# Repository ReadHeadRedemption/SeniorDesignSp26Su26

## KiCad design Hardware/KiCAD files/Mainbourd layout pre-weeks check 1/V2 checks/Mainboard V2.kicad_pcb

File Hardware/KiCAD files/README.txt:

The master schematic is within "Senior design mainboard32826 backup" 

This was the version that everything was verified in as of 4/10/2026

Then for the sake of layout, and neatness broken out into their own project files for each discrete board.
This includes swapping and non-swapping

as of 6/4/2026 

Mainbourd layout pre-weeks check 1 has most up to date version of mainboard PCB this will eventually be made neater again as development continues but this is noted to avoid mistakes for now

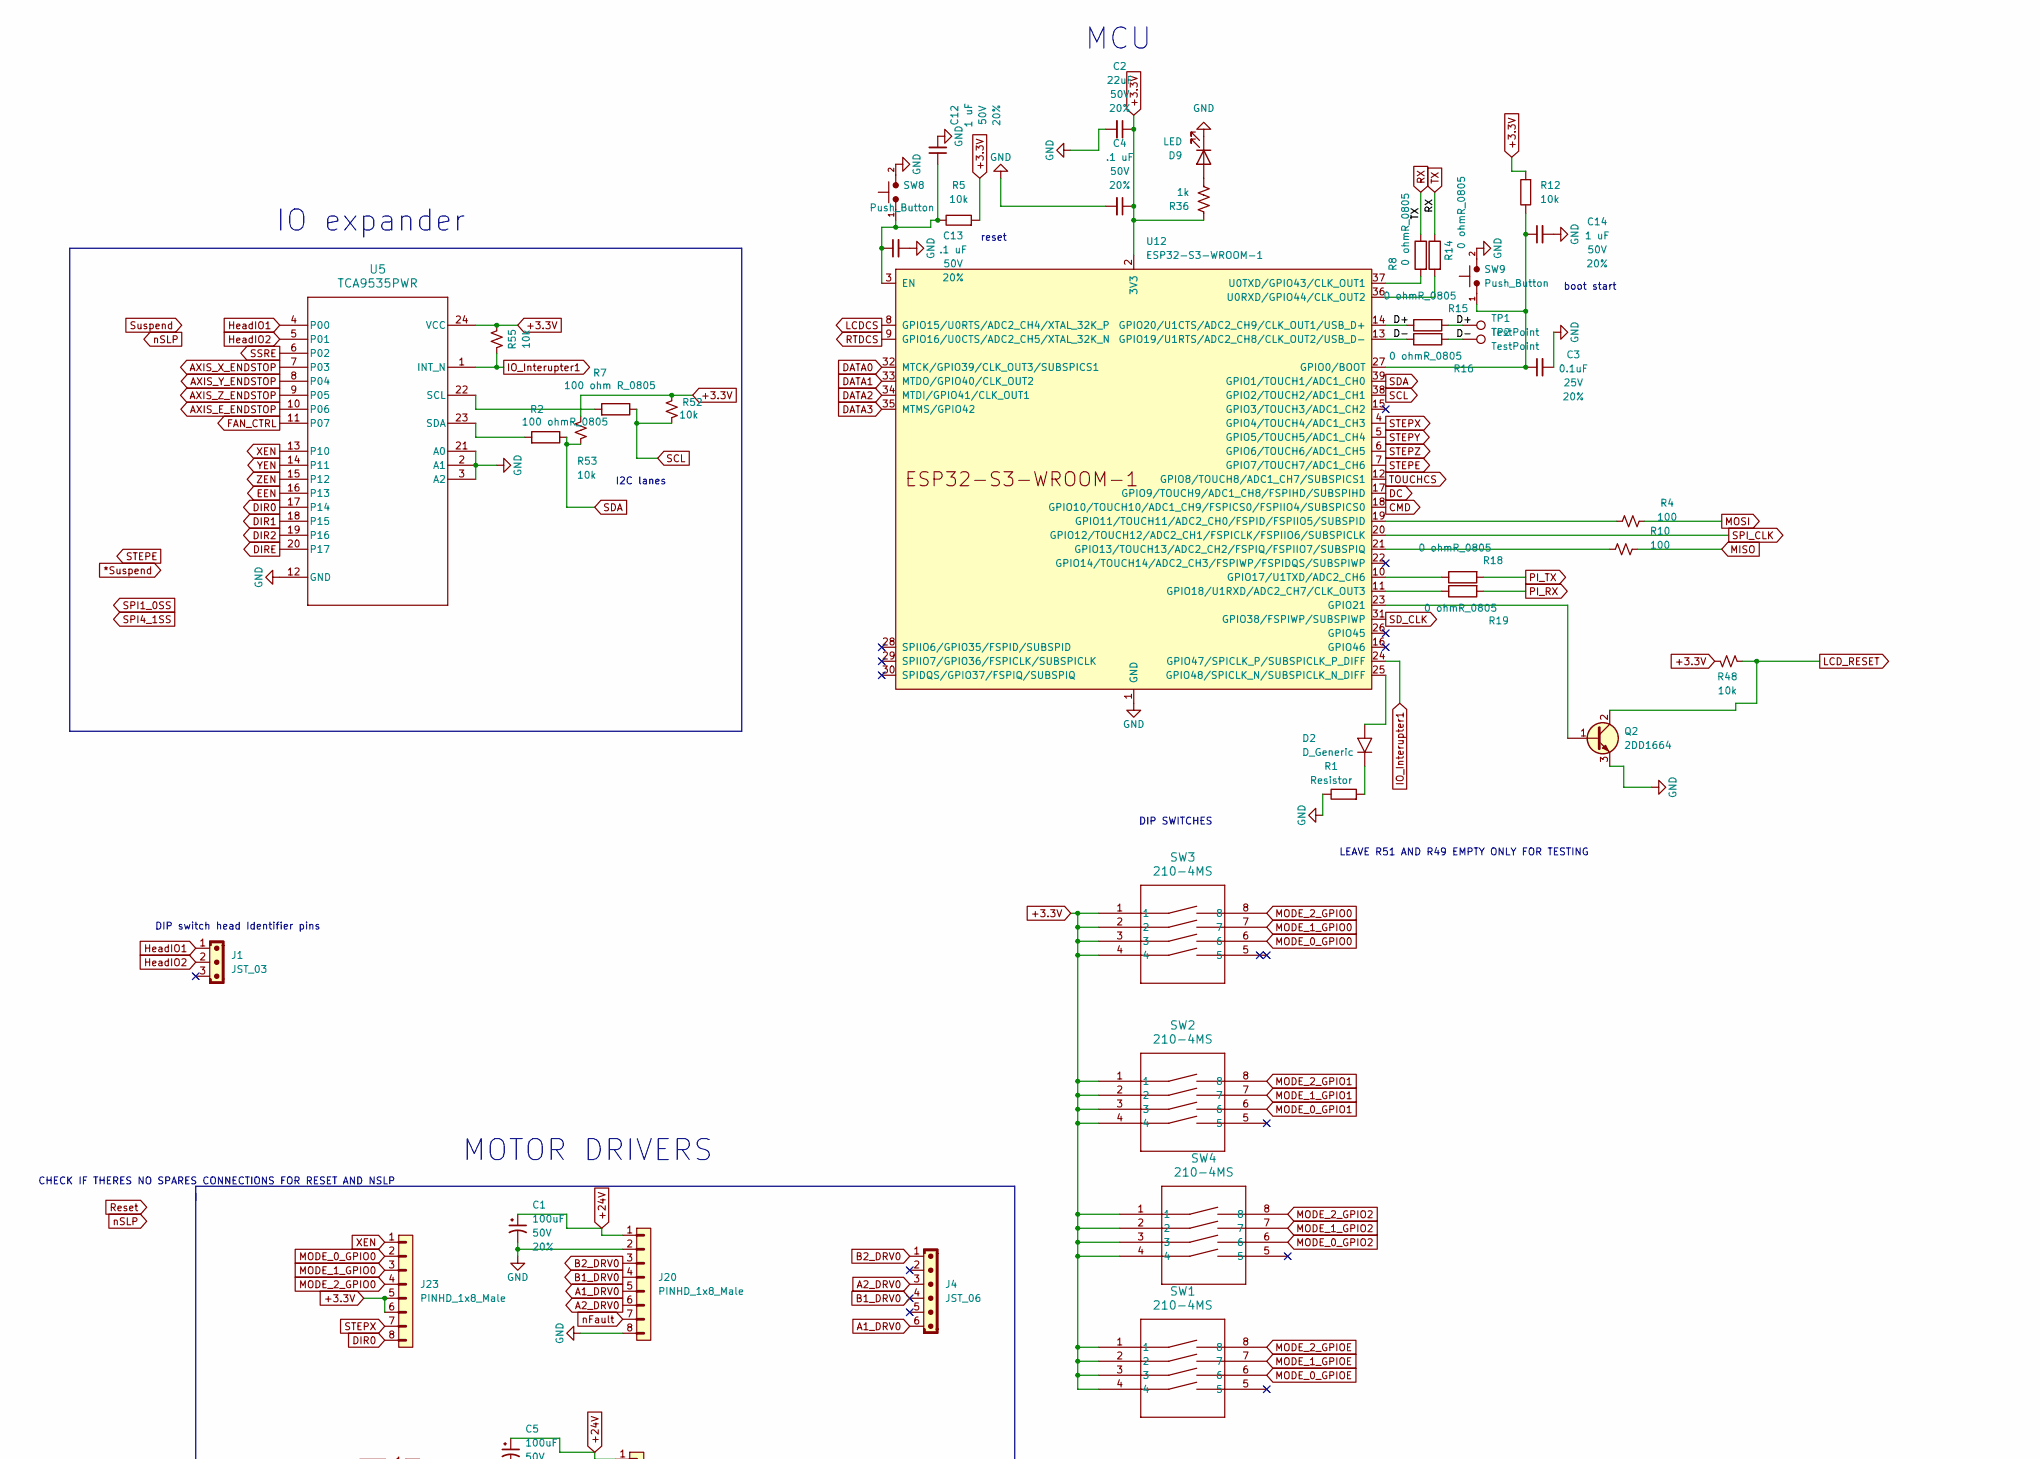
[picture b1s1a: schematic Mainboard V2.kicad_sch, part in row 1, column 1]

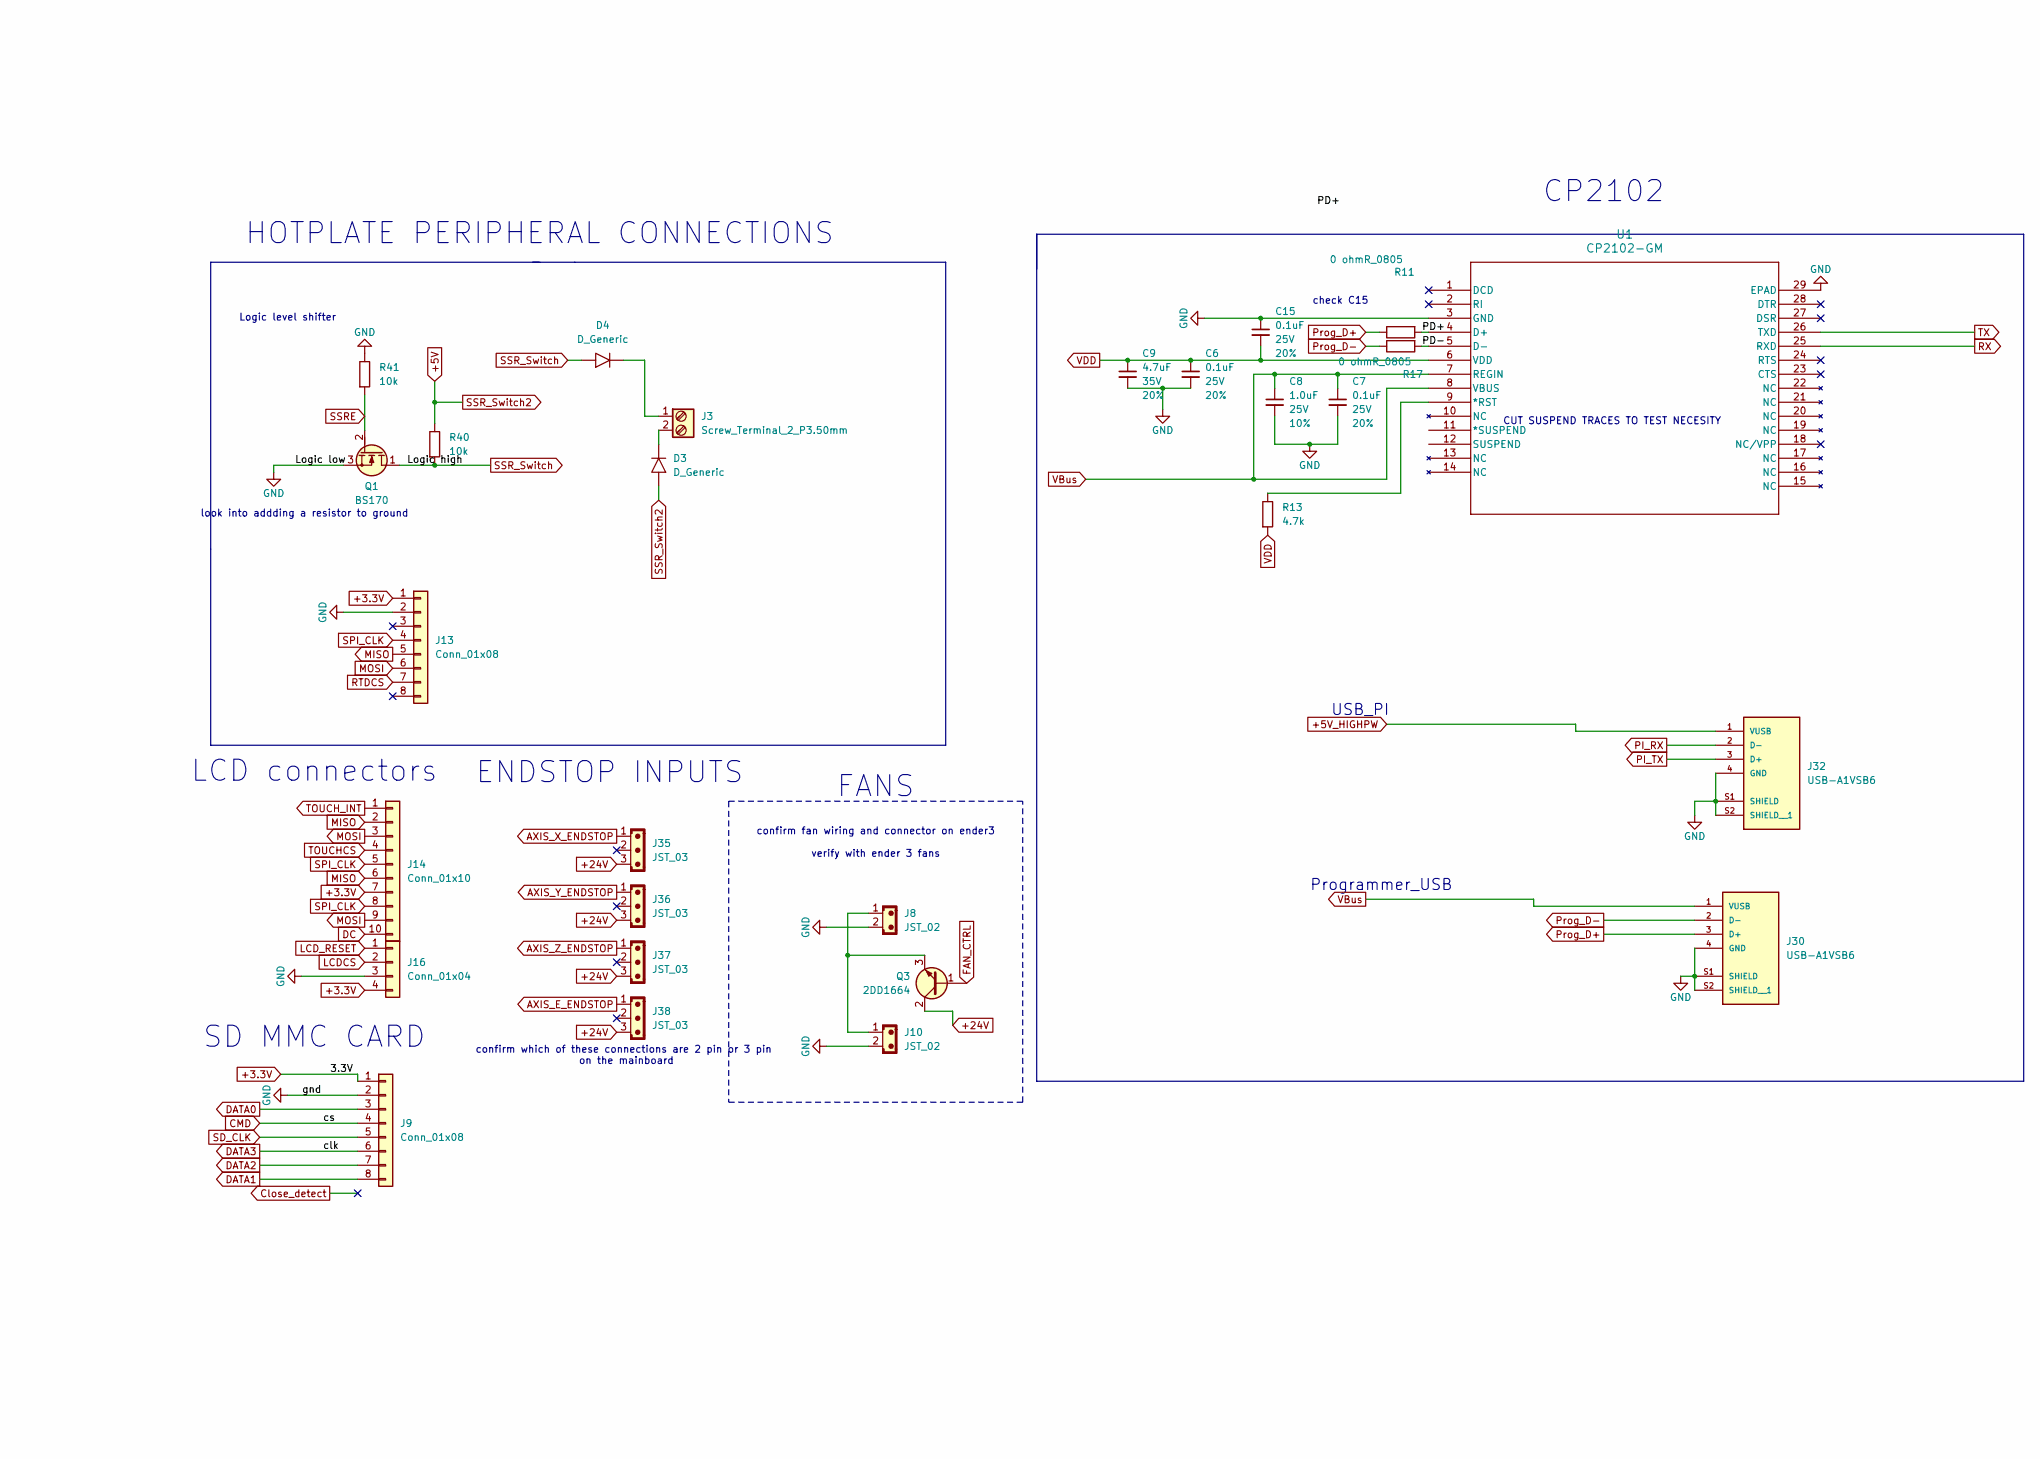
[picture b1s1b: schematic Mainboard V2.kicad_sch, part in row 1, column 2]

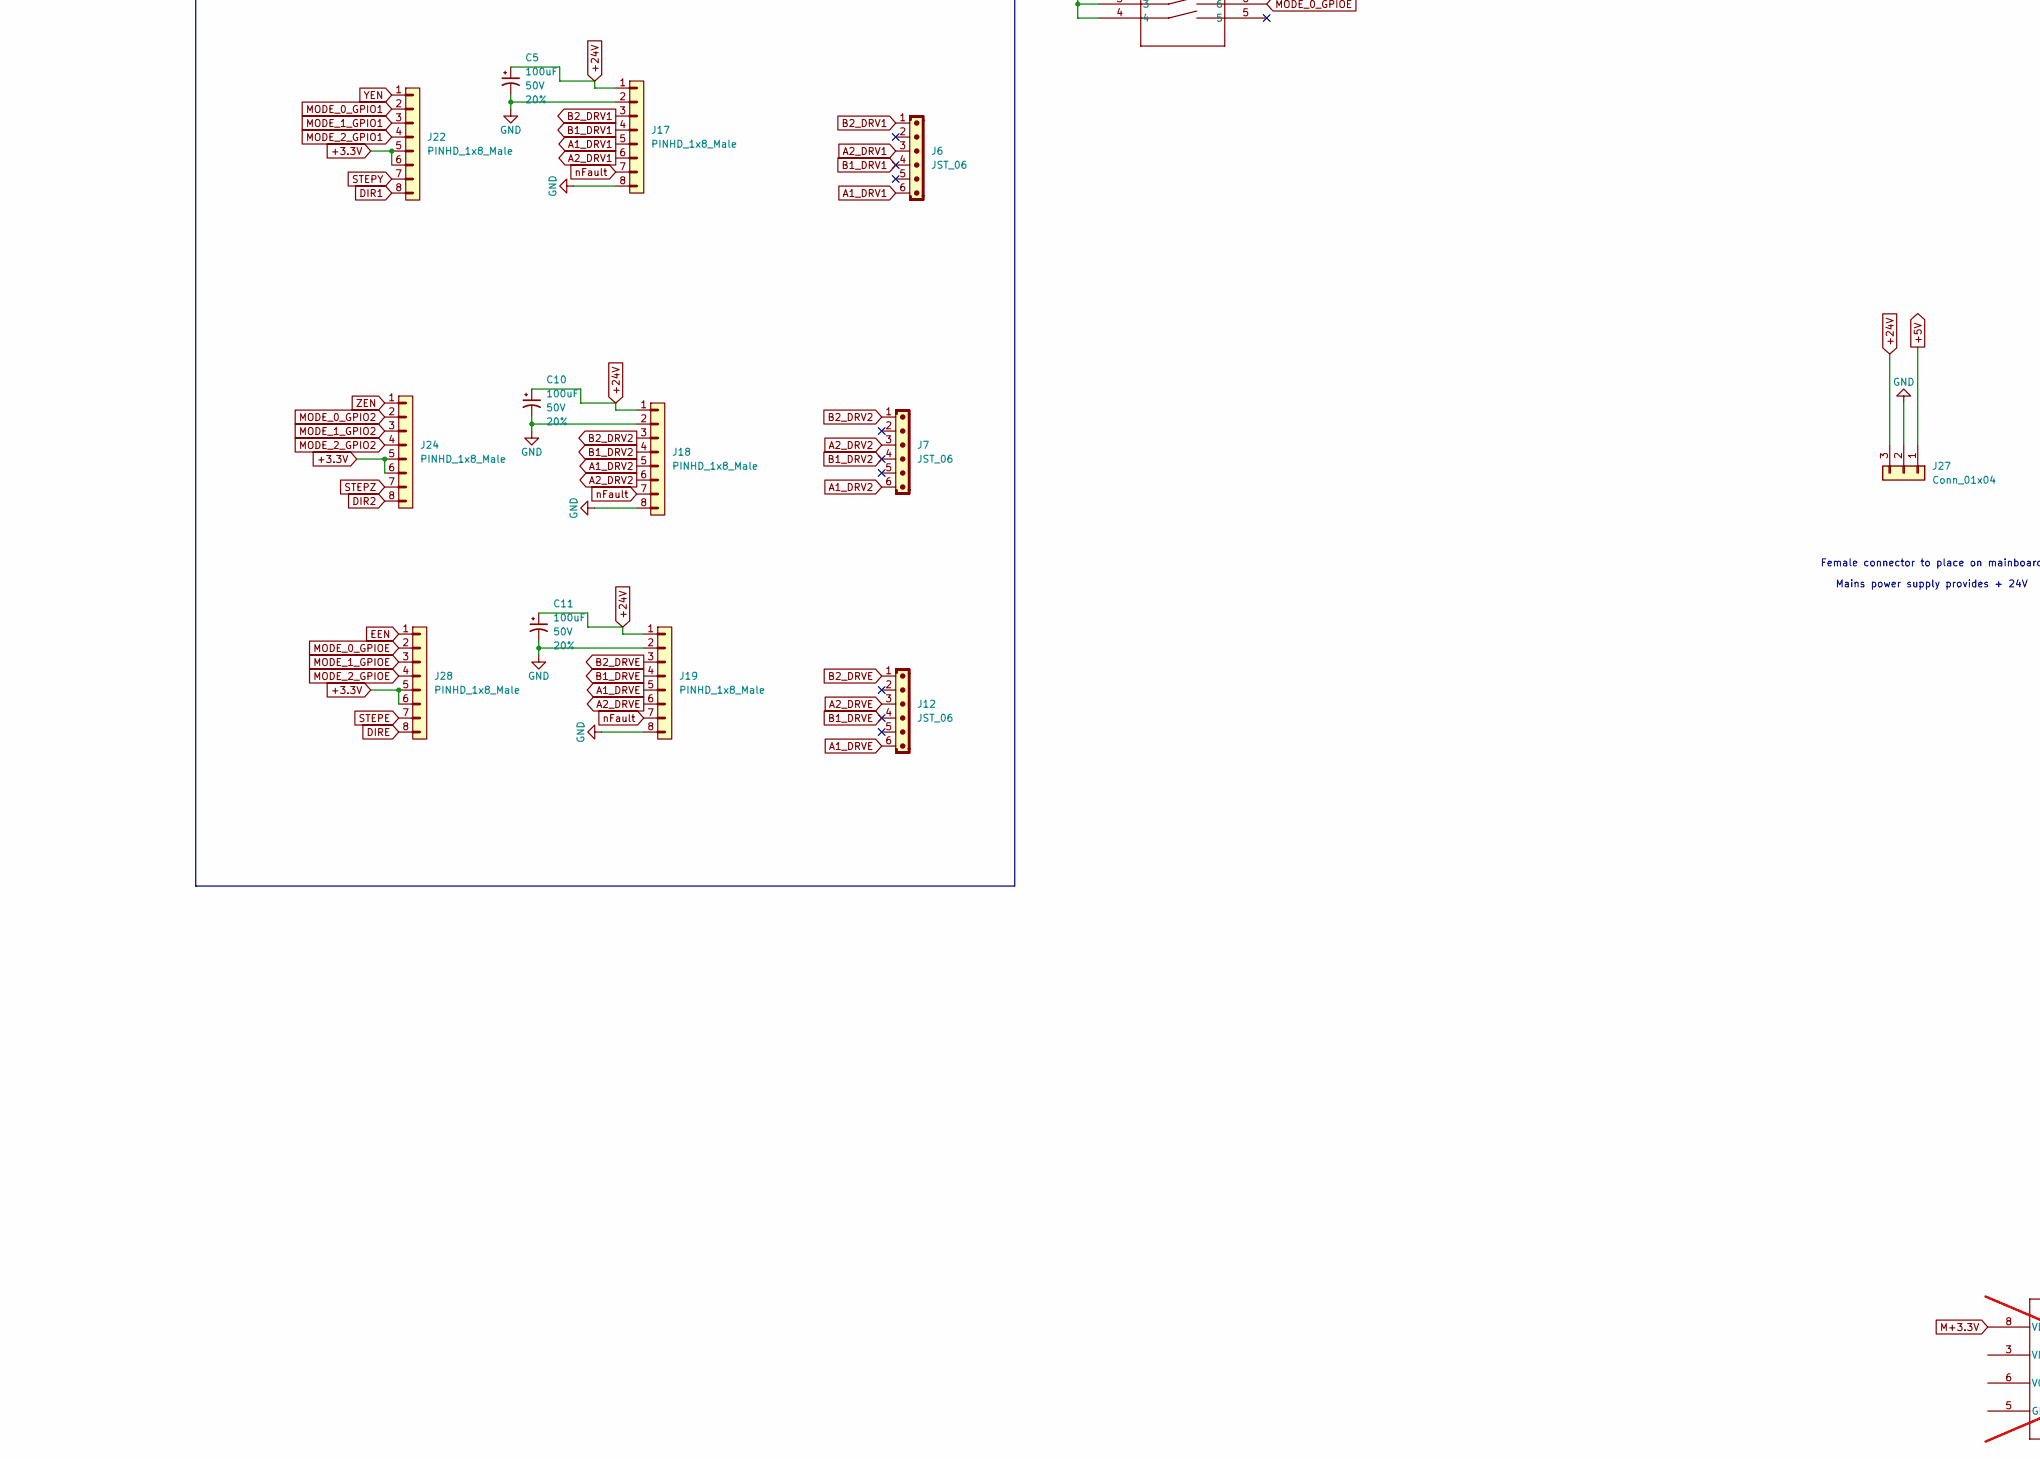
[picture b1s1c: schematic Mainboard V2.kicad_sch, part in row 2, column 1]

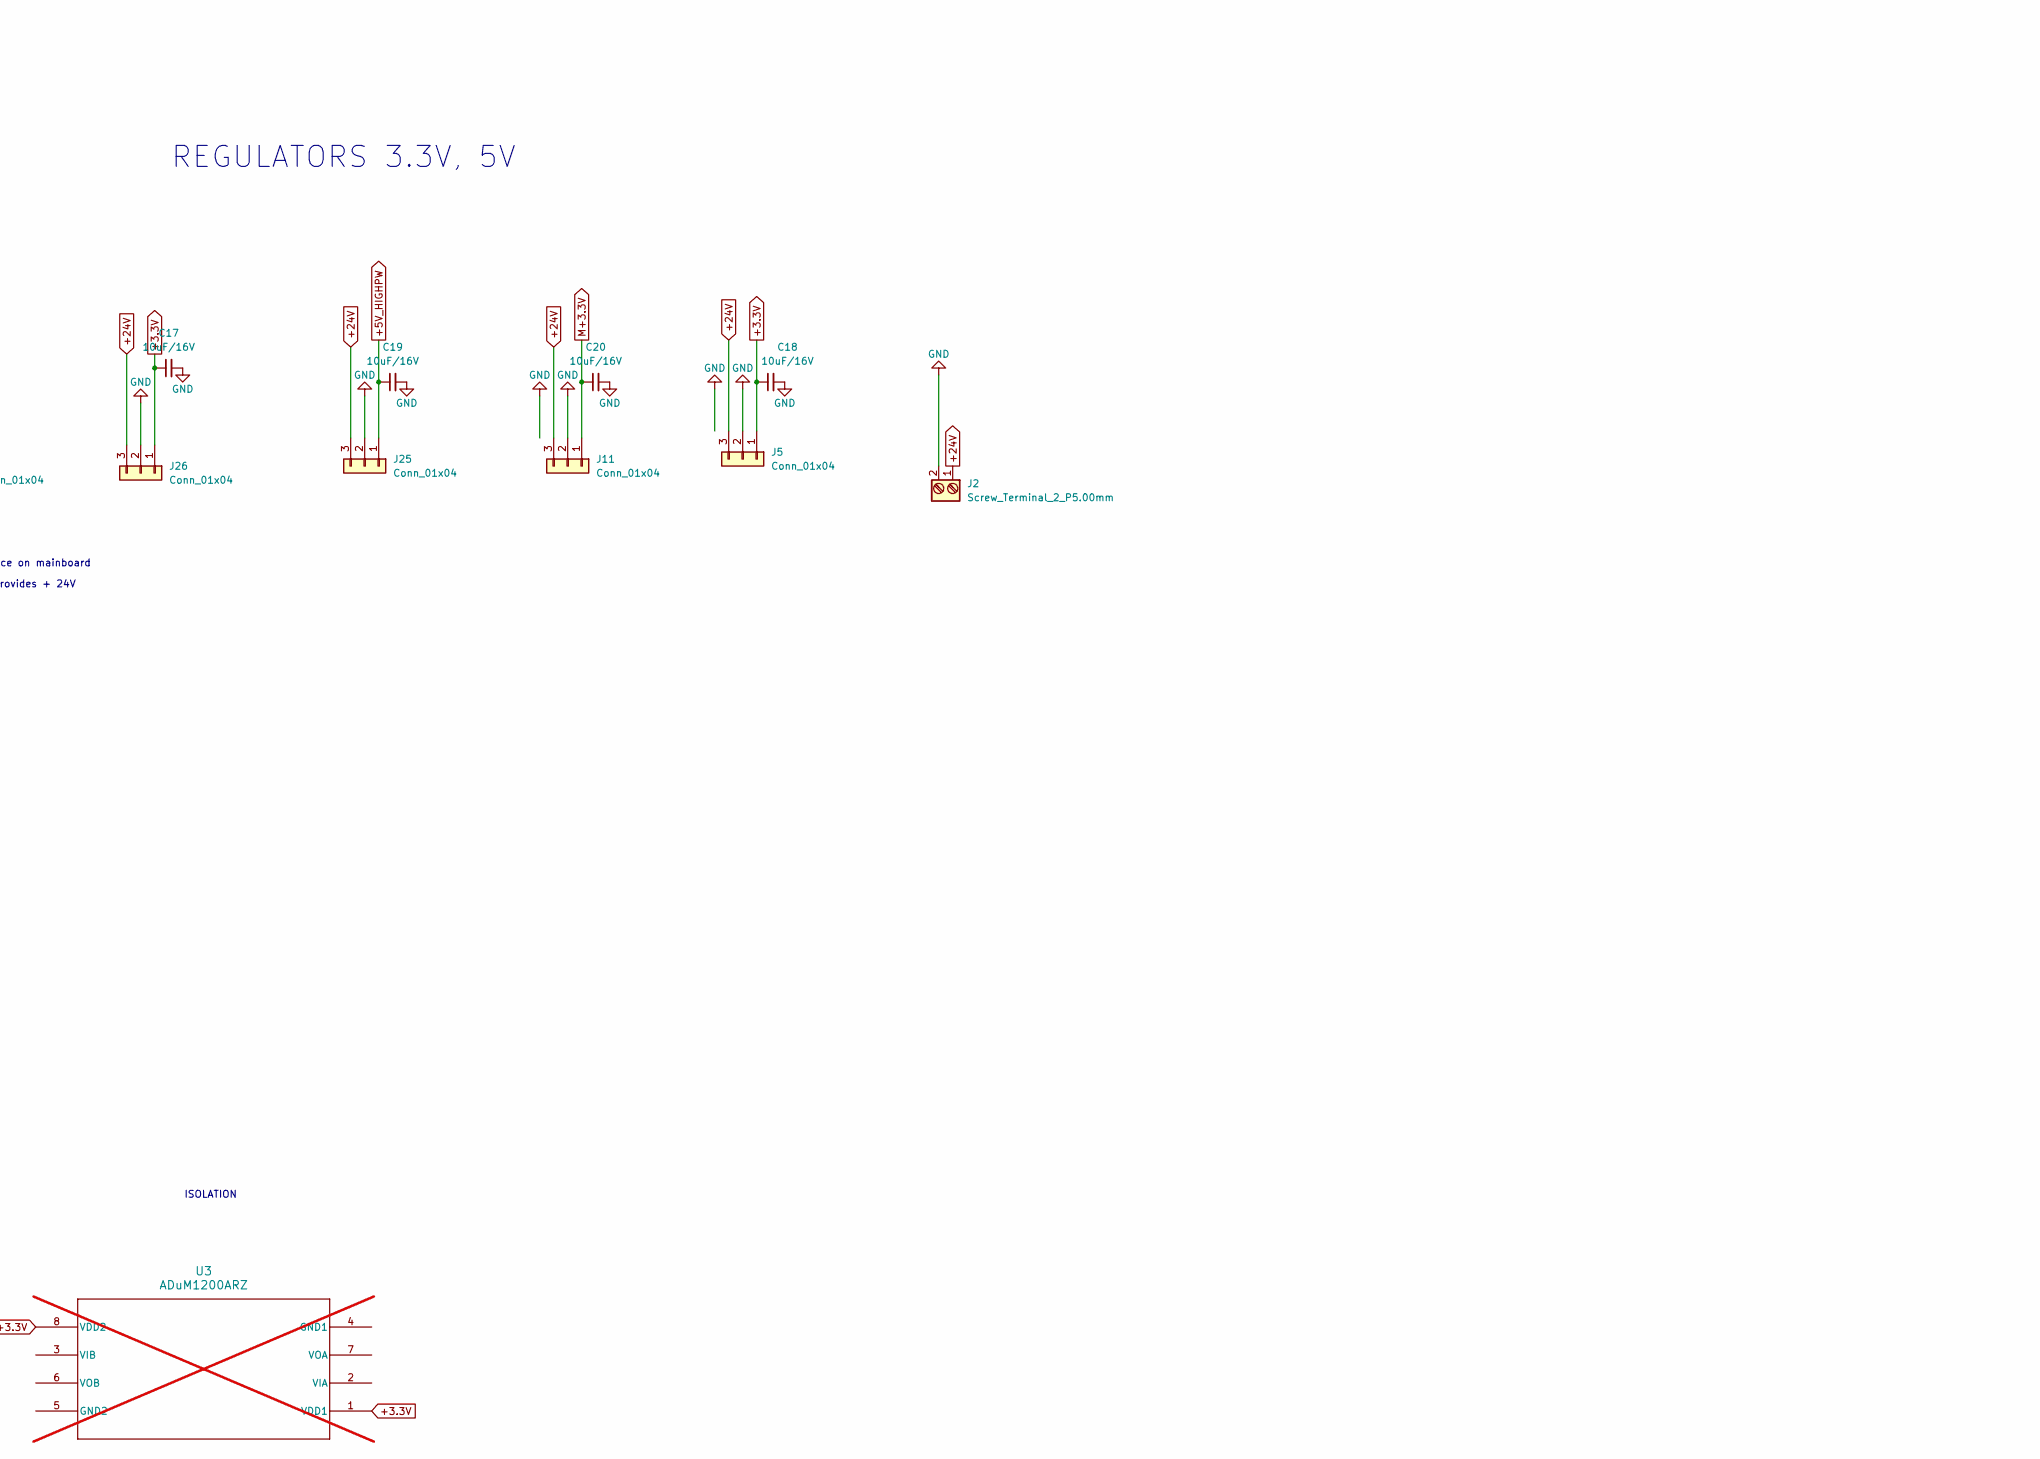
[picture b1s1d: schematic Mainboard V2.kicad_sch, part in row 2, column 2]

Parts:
C1, C5, C10, C11: 100uF; C_Rect_L11.0mm_W3.5mm_P10.00mm_MKT; Voltage 50V; Tolerance 20%
C2: 22uF; C_1210_3225Metric; Voltage 50V; Tolerance 20%
C3, C6, C7, C15: 0.1uF; C_0805_2012Metric; Voltage 25V; Tolerance 20%
C4, C13: .1 uF; C_1210_3225Metric; Voltage 50V; Tolerance 20%
C8: 1.0uF; C_0805_2012Metric; Voltage 25V; Tolerance 10%
C9: 4.7uF; C_0805_2012Metric; Voltage 35V; Tolerance 20%
C12, C14: 1 uF; C_1210_3225Metric; Voltage 50V; Tolerance 20%
C17, C18, C19, C20: 10uF_1210_35V; C_1210_3225Metric; Part Number GMK325BJ106MN-T; JLCPCB ID C172721
D2: D_Generic
D3, D4: D_Generic; D_DO-201AD_P15.24mm_Horizontal
D9: LED; LED_0603_1608Metric
J1, J35, J36, J37, J38: JST_03; JST_EH_B3B-EH-A_1x03_P2.50mm_Vertical
J2: Screw_Terminal_2_P5.00mm; TerminalBlock_Phoenix_PT-1,5-2-5.0-H_1x02_P5.00mm_Horizontal
J3: Screw_Terminal_2_P3.50mm; TerminalBlock_Phoenix_PT-1,5-2-3.5-H_1x02_P3.50mm_Horizontal
J4, J6, J7, J12: JST_06; JST_EH_B6B-EH-A_1x06_P2.50mm_Vertical
J5, J11, J25, J26, J27: Conn_01x04; 1x03_P2.54mm
J8, J10: JST_02; JST_EH_B2B-EH-A_1x02_P2.50mm_Vertical
J9, J13: Conn_01x08; 1x08_P2.54mm
J14: Conn_01x10; 1x10_P2.54mm
J16: Conn_01x04; 1x04_P2.54mm
J17, J18, J19, J20, J22, J23, J24, J28: PINHD_1x8_Male; PinHeader_1x08_P2.54mm_Vertical
J30, J32: USB-A1VSB6; USB_A_Kycon_KUSBX-AS1N-B_Horizontal; PARTREV D
Q1: BS170; TO-92_Inline_Wide_DGS
Q2, Q3: 2DD1664; SOT-89-3
R1: Resistor; R_Axial_DIN0207_L6.3mm_D2.5mm_P10.16mm_Horizontal
R2: 100 ohmR_0805; R_0805_2012Metric
R4, R10: 100; R_0805_2012Metric
R5, R12, R40, R41: 10k; R_Axial_DIN0207_L6.3mm_D2.5mm_P10.16mm_Horizontal
R7: 100 ohm R_0805; R_0805_2012Metric
R8, R11, R14, R15, R16, R17, R18, R19: 0 ohmR_0805; R_0805_2012Metric
R13: 4.7k; R_Axial_DIN0207_L6.3mm_D2.5mm_P10.16mm_Horizontal
R36: 1k; R_1206_3216Metric_Pad1.30x1.75mm_HandSolder
R48: 10k; R_0603_1608Metric
R52, R53: 10k; LED_0805_2012Metric
R55: 10k; R_0805_2012Metric
SW1, SW2, SW3, SW4: 210-4MS; DIP8_210-4_CTS
SW8, SW9: Push_Button; SW_PUSH_6mm
TP1, TP2: TestPoint; TestPoint_Loop_D2.54mm_Drill1.5mm_Beaded
U1: CP2102-GM; QFN28_5X5_SIL
U3: ADuM1200ARZ; R_8_ADI; not fitted
U5: TCA9535PWR; PW0024A_N
U12: ESP32-S3-WROOM-1

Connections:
+3.3V: C2.1, C4.1, C17.1, C18.1, J5.1, J9.1, J13.1, J14.7, J16.4, J22.5, J22.6, J23.5, J23.6, J24.5, J24.6, J26.1, J28.5, J28.6, R5.1, R12.1, R36.1, R48.1, R52.2, R53.2, R55.1, SW1.1, SW1.2, SW1.3, SW1.4, SW2.1, SW2.2, SW2.3, SW2.4, SW3.1, SW3.2, SW3.3, SW3.4, SW4.1, SW4.2, SW4.3, SW4.4, U3.1 (VDD1), U5.24 (VCC), U12.2 (3V3)
+5V: D3.2 (A), J27.1, R40.2
+5V_HIGHPW: C19.1, J25.1, J32.1 (VUSB)
+24V: C1.1, C5.1, C10.1, C11.1, J2.1, J5.3, J11.3, J17.1, J18.1, J19.1, J20.1, J25.3, J26.3, J27.3, J35.3, J36.3, J37.3, J38.3, Q3.2 (C)
/D+: R15.1, R15.2, TP1.1 (1_1), U12.14 (GPIO20/U1CTS/ADC2_CH9/CLK_OUT1/USB_D+)
/D-: R16.1, R16.2, TP2.1 (1_1), U12.13 (GPIO19/U1RTS/ADC2_CH8/CLK_OUT2/USB_D-)
/PD+: R11.1, U1.4 (D+)
/PD-: R17.1, U1.5 (D-)
A1_DRV0: J4.6, J20.5
A1_DRV1: J6.6, J17.5
A1_DRV2: J7.6, J18.5
A1_DRVE: J12.6, J19.5
A2_DRV0: J4.3, J20.6
A2_DRV1: J6.3, J17.6
A2_DRV2: J7.3, J18.6
A2_DRVE: J12.3, J19.6
AXIS_E_ENDSTOP: J38.1, U5.10 (P06)
AXIS_X_ENDSTOP: J35.1, U5.7 (P03)
AXIS_Y_ENDSTOP: J36.1, U5.8 (P04)
AXIS_Z_ENDSTOP: J37.1, U5.9 (P05)
B1_DRV0: J4.4, J20.4
B1_DRV1: J6.4, J17.4
B1_DRV2: J7.4, J18.4
B1_DRVE: J12.4, J19.4
B2_DRV0: J4.1, J20.3
B2_DRV1: J6.1, J17.3
B2_DRV2: J7.1, J18.3
B2_DRVE: J12.1, J19.3
CMD: J9.4, U12.18 (GPIO10/TOUCH10/ADC1_CH9/FSPICS0/FSPIIO4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)
DATA0: J9.3, U12.32 (MTCK/GPIO39/CLK_OUT3/SUBSPICS1)
DATA1: J9.8, U12.33 (MTDO/GPIO40/CLK_OUT2)
DATA2: J9.7, U12.34 (MTDI/GPIO41/CLK_OUT1)
DATA3: J9.6, U12.35 (MTMS/GPIO42)
DC: J14.10, U12.17 (GPIO9/TOUCH9/ADC1_CH8/FSPIHD/SUBSPIHD)
DIR0: J23.8, U5.17 (P14)
DIR1: J22.8, U5.18 (P15)
DIR2: J24.8, U5.19 (P16)
DIRE: J28.8, U5.20 (P17)
EEN: J28.1, U5.16 (P13)
FAN_CTRL: Q3.1 (B), U5.11 (P07)
GND: C1.2, C2.2, C3.2, C4.2, C5.2, C6.2, C7.2, C8.2, C9.2, C10.2, C11.2, C12.2, C13.2, C14.2, C15.1, C17.2, C18.2, C19.2, C20.2, D9.1 (K), J2.2, J5.2, J8.2, J9.2, J10.2, J11.2, J13.2, J16.3, J17.2, J17.8, J18.2, J18.8, J19.2, J19.8, J20.2, J20.8, J25.2, J26.2, J27.2, J30.4 (GND), J30.S1 (SHIELD), J30.S2 (SHIELD__1), J32.4 (GND), J32.S1 (SHIELD), J32.S2 (SHIELD__1), Q1.3 (S), Q2.3 (E), R1.2, R41.2, SW8.2, SW9.2, U1.3 (GND), U1.29 (EPAD), U5.2 (A1), U5.3 (A2), U5.12 (GND), U5.21 (A0), U12.1 (GND), U12.40 (GND), U12.41 (GND); also elsewhere on the board
HeadIO1: J1.1, U5.4 (P00)
HeadIO2: J1.2, U5.5 (P01)
IO_Interupter1: R55.2, U5.1 (INT_N), U12.24 (GPIO47/SPICLK_P/SUBSPICLK_P_DIFF)
LCDCS: J16.2, U12.8 (GPIO15/U0RTS/ADC2_CH4/XTAL_32K_P)
LCD_RESET: J16.1, Q2.2 (C), R48.2
M+3.3V: C20.1, J11.1, U3.8 (VDD2)
MISO: J13.5, J14.2, J14.6, R10.2
MODE_0_GPIO0: J23.2, SW3.6
MODE_0_GPIO1: J22.2, SW2.6
MODE_0_GPIO2: J24.2, SW4.6
MODE_0_GPIOE: J28.2, SW1.6
MODE_1_GPIO0: J23.3, SW3.7
MODE_1_GPIO1: J22.3, SW2.7
MODE_1_GPIO2: J24.3, SW4.7
MODE_1_GPIOE: J28.3, SW1.7
MODE_2_GPIO0: J23.4, SW3.8
MODE_2_GPIO1: J22.4, SW2.8
MODE_2_GPIO2: J24.4, SW4.8
MODE_2_GPIOE: J28.4, SW1.8
MOSI: J13.6, J14.3, J14.9, R4.2
unnamed: D2.2 (A), U12.25 (GPIO48/SPICLK_N/SUBSPICLK_N_DIFF)
unnamed: D2.1 (K), R1.1
unnamed: D3.1 (K), J3.2
unnamed: D4.1 (K), J3.1
unnamed: D9.2 (A), R36.2
unnamed: Q2.1 (B), U12.23 (GPIO21)
unnamed: J8.1, J10.1, Q3.3 (E)
unnamed: R13.2, U1.9 (*RST)
unnamed: R7.1, U5.22 (SCL)
unnamed: R2.1, U5.23 (SDA)
unnamed 71: C12.1, C13.1, R5.2, SW8.1, U12.3 (EN); also elsewhere on the board
unnamed: C3.1, C14.1, R12.2, SW9.1, U12.27 (GPIO0/BOOT)
unnamed: R4.1, U12.19 (GPIO11/TOUCH11/ADC2_CH0/FSPID/FSPIIO5/S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)
unnamed: R10.1, U12.21 (GPIO13/TOUCH13/ADC2_CH2/FSPIQ/FSPIIO7/S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)
unnamed: R18.2, U12.10 (GPIO17/U1TXD/ADC2_CH6)
unnamed: R19.2, U12.11 (GPIO18/U1RXD/ADC2_CH7/CLK_OUT3)
unnamed: R14.1, U12.36 (U0RXD/GPIO44/CLK_OUT2)
unnamed: R8.1, U12.37 (U0TXD/GPIO43/CLK_OUT1)
PI_RX: J32.2 (D-), R19.1
PI_TX: J32.3 (D+), R18.1
Prog_D+: J30.3 (D+), R11.2
Prog_D-: J30.2 (D-), R17.2
RTDCS: J13.7, U12.9 (GPIO16/U0CTS/ADC2_CH5/XTAL_32K_N)
RX: R8.2, R14.2, U1.25 (RXD), U1.26 (TXD)
SCL: R7.2, R52.1, U12.38 (GPIO2/TOUCH2/ADC1_CH1)
SDA: R2.2, R53.1, U12.39 (GPIO1/TOUCH1/ADC1_CH0)
SD_CLK: J9.5, U12.31 (GPIO38/FSPIWP/SUBSPIWP)
SPI_CLK: J13.4, J14.5, J14.8, U12.20 (GPIO12/TOUCH12/ADC2_CH1/FSPICLK/FSPIIO6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)
SSRE: Q1.2 (G), R41.1, U5.6 (P02)
SSR_Switch: D4.2 (A), Q1.1 (D), R40.1
STEPE: J28.7, U12.7 (GPIO7/TOUCH7/ADC1_CH6)
STEPX: J23.7, U12.4 (GPIO4/TOUCH4/ADC1_CH3)
STEPY: J22.7, U12.5 (GPIO5/TOUCH5/ADC1_CH4)
STEPZ: J24.7, U12.6 (GPIO6/TOUCH6/ADC1_CH5)
TOUCHCS: J14.4, U12.12 (GPIO8/TOUCH8/ADC1_CH7/SUBSPICS1)
TOUCH_INT: J14.1
VBus: C7.1, C8.1, J30.1 (VUSB), U1.7 (REGIN), U1.8 (VBUS)
VDD: C6.1, C9.1, C15.2, R13.1, U1.6 (VDD)
XEN: J23.1, U5.13 (P10)
YEN: J22.1, U5.14 (P11)
ZEN: J24.1, U5.15 (P12)
nFault: J17.7, J18.7, J19.7, J20.7

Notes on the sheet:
ISOLATION
HOTPLATE PERIPHERAL CONNECTIONS
CHECK IF THERES NO SPARES CONNECTIONS FOR RESET AND NSLP
boot start
I2C lanes
USB_PI
Mains power supply provides + 24V
Female connector to place on mainboard
confirm which of these connections are 2 pin or 3 pin on the mainboard
ENDSTOP INPUTS
IO expander
look into addding a resistor to ground
DIP SWITCHES
LCD connectors
LEAVE R51 AND R49 EMPTY ONLY FOR TESTING
CP2102
CUT SUSPEND TRACES TO TEST NECESITY
check C15
SD MMC CARD
FANS
DIP switch head Identifier pins
MCU
REGULATORS 3.3V, 5V
reset
Logic level shifter
MOTOR DRIVERS
confirm fan wiring and connector on ender3 verify with ender 3 fans
Programmer_USB

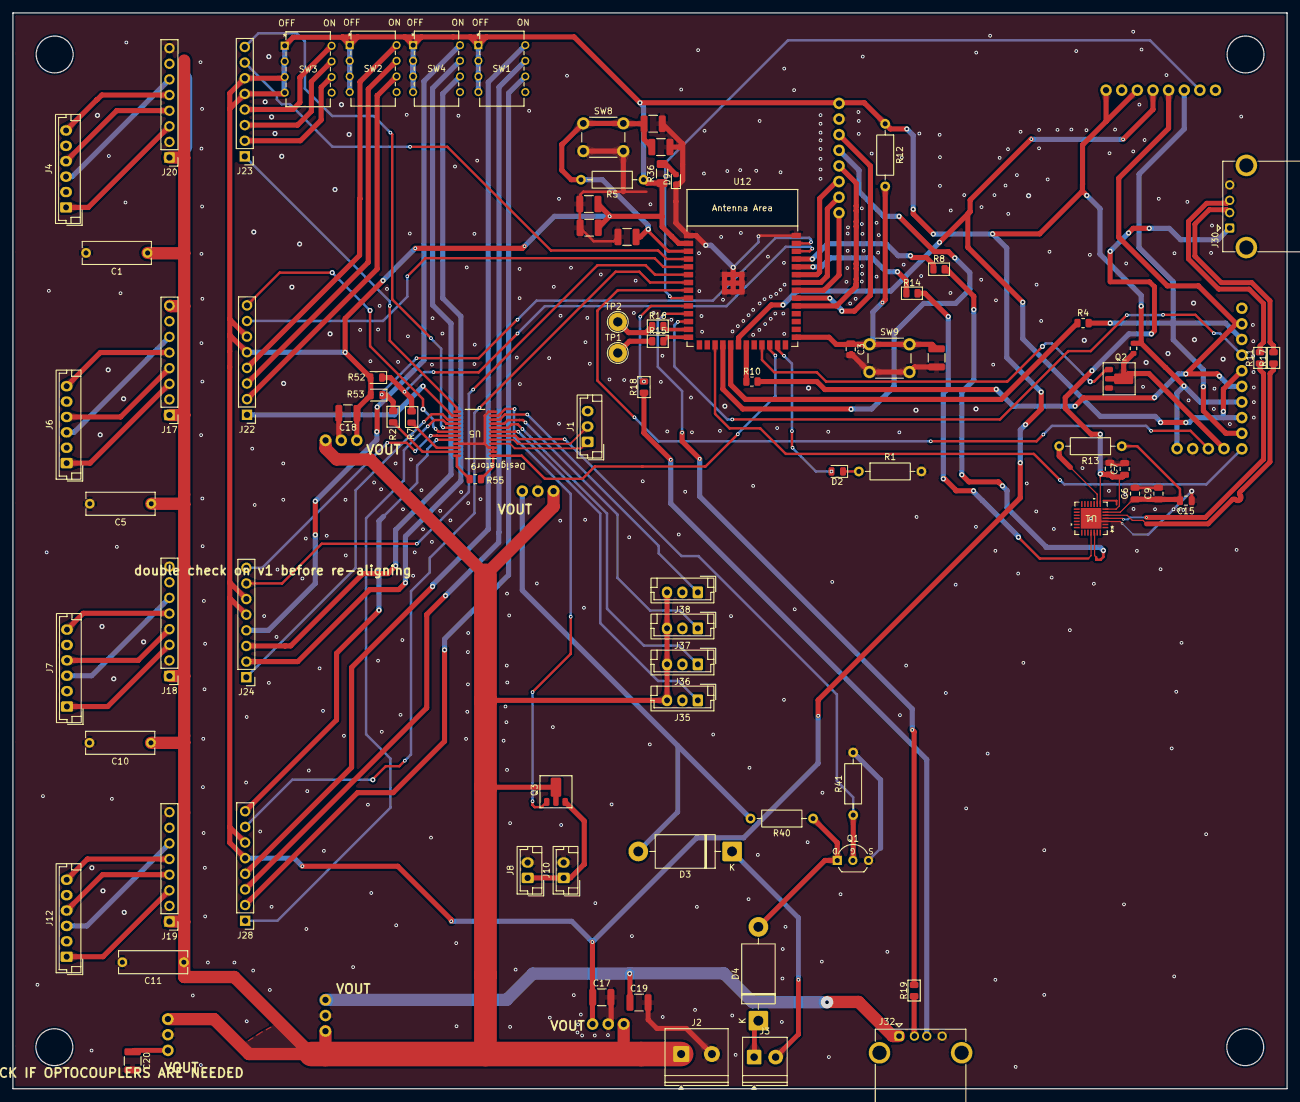
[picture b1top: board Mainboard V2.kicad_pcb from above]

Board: 2 copper layers, 207.0 x 174.8 mm, 93 parts (0 on the bottom side), 102 nets.

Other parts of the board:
C4#2: 10uF; C_1210_3225Metric

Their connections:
GND: C4#2.2; also elsewhere on the board
unnamed 71: C4#2.1; also elsewhere on the board

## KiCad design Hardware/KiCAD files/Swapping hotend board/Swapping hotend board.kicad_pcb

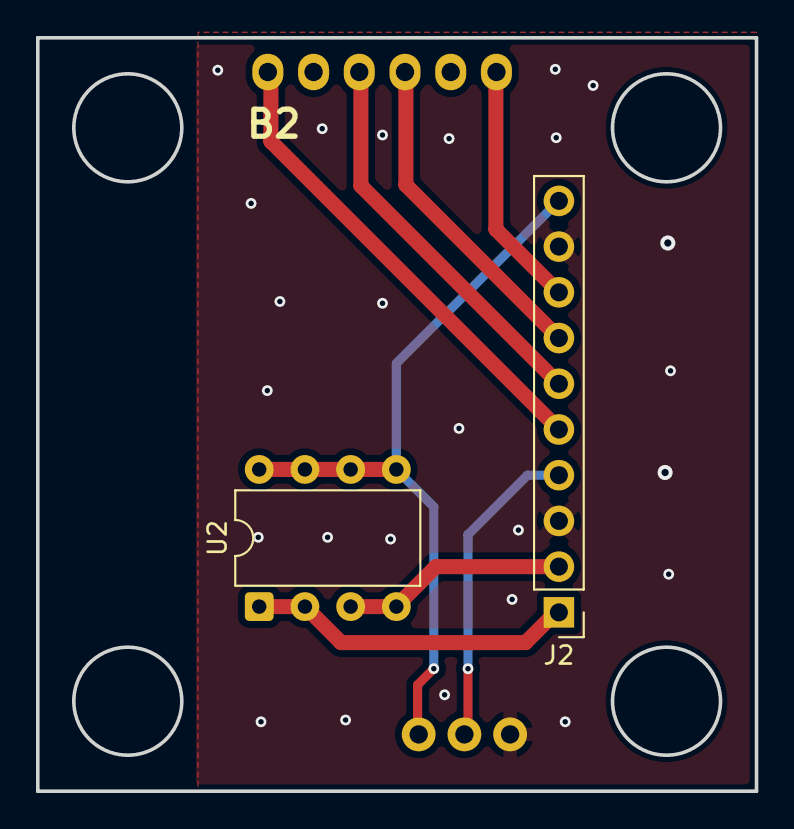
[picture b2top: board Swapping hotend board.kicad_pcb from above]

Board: 2 copper layers, 39.9 x 41.9 mm, 4 parts (1 on the bottom side), 9 nets.

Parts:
J2: PINHD_1x10_Male; PinHeader_1x10_P2.54mm_Vertical
J3: JST_06; Pins_1x06_2.54mm_TH_SWD
J18: JST_1mm_3_Vertical; 1x03_P2.54mm
U2: DIP-8_W7.62mm

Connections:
/A1: J2.8, J3.1
/A2: J2.6, J3.4
/B1: J2.7, J3.3
/B2: J2.5, J3.6
GND: J2.3, J2.9, J18.1
unnamed: J2.4, J18.2
unnamed: J2.1, U2.1 (SW1-P1), U2.2 (SW1-P2)
unnamed: J2.10, J18.3, U2.5 (SW1-P1-input), U2.6 (SW1-P2-input), U2.7 (SW2-P1-input), U2.8 (SW2-P2-input)
unnamed: J2.2, U2.3 (SW2-P1), U2.4 (SW2-P4)

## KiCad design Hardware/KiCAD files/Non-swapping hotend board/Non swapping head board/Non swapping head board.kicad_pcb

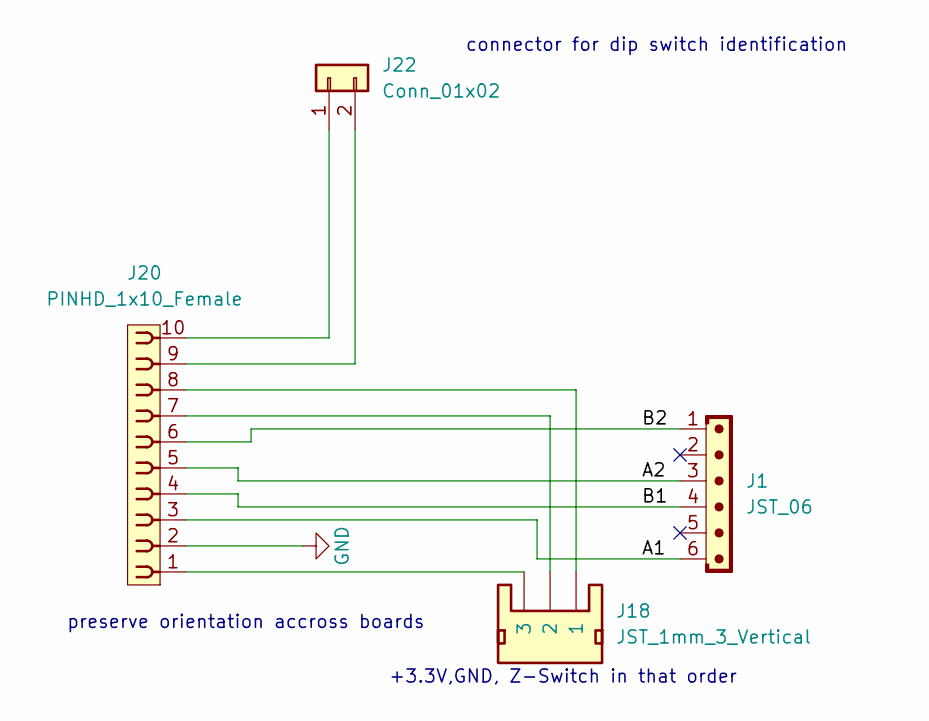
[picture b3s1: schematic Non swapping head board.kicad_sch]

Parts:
J1: JST_06; JST_EH_B6B-EH-A_1x06_P2.50mm_Vertical
J18: JST_1mm_3_Vertical; 1x03_P2.54mm
J20: PINHD_1x10_Female; PinSocket_1x10_P2.54mm_Horizontal
J22: Conn_01x02; 1x02_P2.54mm

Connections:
/A1: J1.6, J20.3
/A2: J1.3, J20.5
/B1: J1.4, J20.4
/B2: J1.1, J20.6
GND: J20.2
unnamed: J18.1, J20.8
unnamed: J18.2, J20.7
unnamed: J18.3, J20.1
unnamed: J20.10, J22.1
unnamed: J20.9, J22.2

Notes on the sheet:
connector for dip switch identification
+3.3V,GND, Z-Switch in that order
preserve orientation accross boards

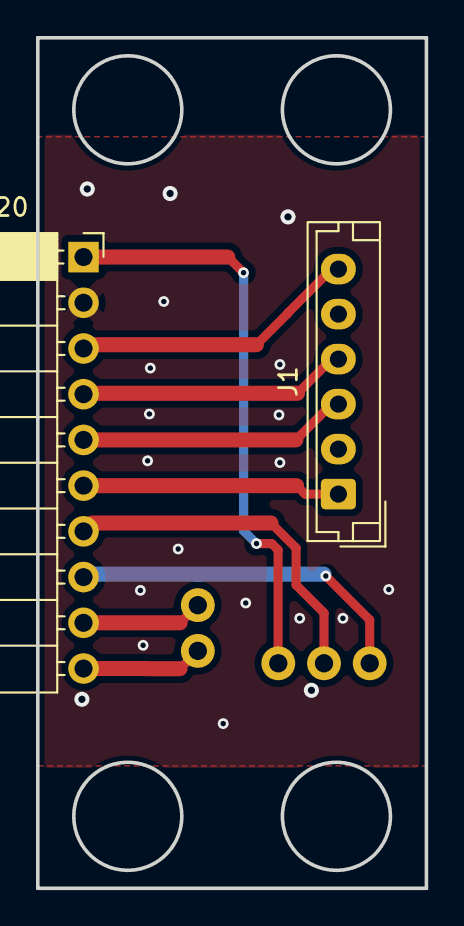
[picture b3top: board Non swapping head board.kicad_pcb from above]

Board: 2 copper layers, 21.6 x 47.2 mm, 4 parts (0 on the bottom side), 9 nets.

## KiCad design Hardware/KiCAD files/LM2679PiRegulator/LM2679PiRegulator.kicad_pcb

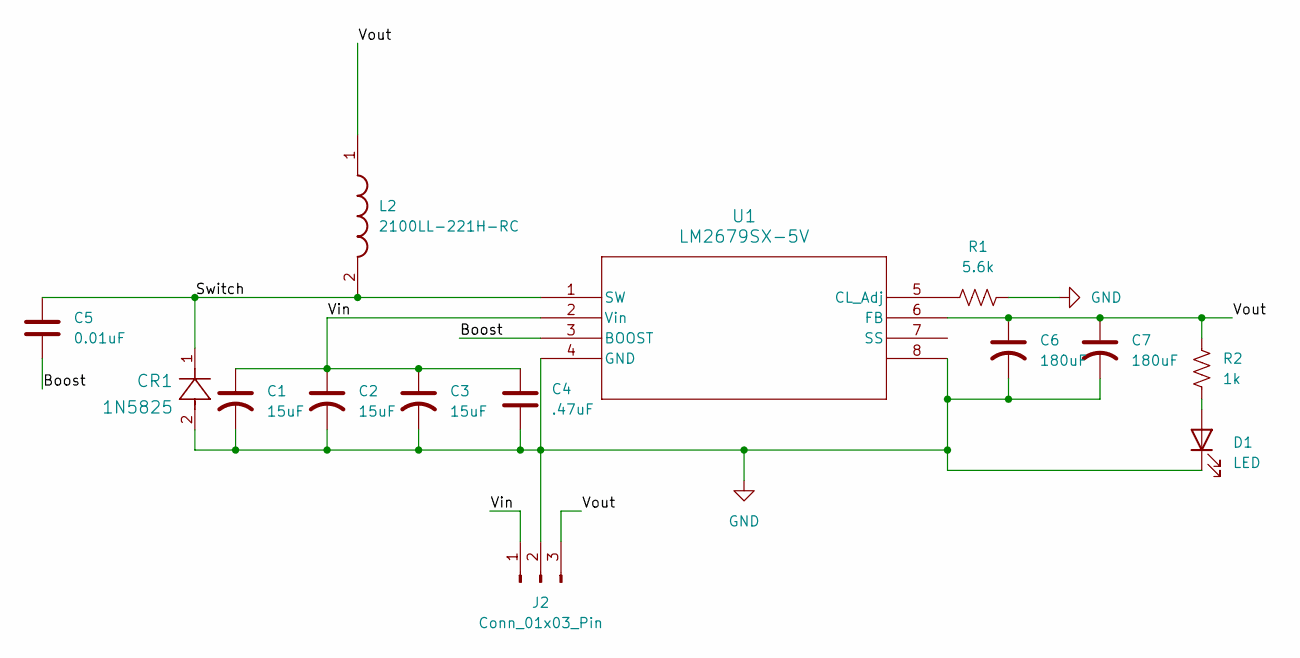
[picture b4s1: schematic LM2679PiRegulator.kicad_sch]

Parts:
C1, C2, C3: 15uF; C_Axial_L3.8mm_D2.6mm_P7.50mm_Horizontal
C4: .47uF; C_Axial_L3.8mm_D2.6mm_P7.50mm_Horizontal
C5: 0.01uF; C_Axial_L3.8mm_D2.6mm_P7.50mm_Horizontal
C6, C7: 180uF; C_Radial_D8.0mm_H7.0mm_P3.50mm
CR1: 1N5825; 1N5825_MCH
D1: LED; LED_1206_3216Metric_Pad1.42x1.75mm_HandSolder
J2: Conn_01x03_Pin; PinHeader_1x03_P2.54mm_Vertical
L2: 2100LL-221H-RC; 2100LL221HRC; Manufacturer_Part_Number 2100LL-221H-RC
R1: 5.6k; R_1206_3216Metric_Pad1.30x1.75mm_HandSolder
R2: 1k; R_1206_3216Metric_Pad1.30x1.75mm_HandSolder
U1: LM2679SX-5V; TS7B

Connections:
/Boost: C5.2, U1.3 (BOOST)
/Switch: C5.1, CR1.1, L2.2, U1.1 (SW)
/Vin: C1.1, C2.1, C3.1, C4.1, J2.1, U1.2 (Vin)
/Vout: C6.1, C7.1, J2.3, L2.1, R2.1, U1.6 (FB)
GND: C1.2, C2.2, C3.2, C4.2, C6.2, C7.2, CR1.2, D1.1 (K), J2.2, R1.2, U1.4 (GND), U1.8
unnamed: D1.2 (A), R2.2
unnamed: R1.1, U1.5 (CL_Adj)
